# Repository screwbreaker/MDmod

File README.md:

# MDmod
Yes, another Mega Drive switchless mod

### Summary
This is another version of the classic switchless MOD for Mega Drive/Genesis.
There are two version of this MOD.
One for Padauk microcontrollers. And one for the old PIC16F630.
For each micro there is a little PCB for help in the installation.

### History
Everything started because I got some Padauk microcontrollers, and I wanted to play with them.
I choose to implement the Mega Drive switchless mod, because it seem very appropriate, as a basic program for microcontrollers.

Unfortunately, I've never enought free time to work on this project.
When I finally managed to make it the padauk microcontrollers where out of stock.
They still cheap, but not easy to found now.
So, since SDCC also handle PIC microcontrollers, I thought it was nice to port the code for the old PIC16F630.

I also made some little PCB, to make the installation simpler.

That's it, that's why now there is another, or better, onother two switchless mod for Mega Drive.

### How it work
This version is very simple, it only allow to switch between the different regions, JP, USA, EU
There is no way to change only the region or only the video mode.

#### How to change region
Hold down the reset button.
After 2 seconds the region led start to blink fast.
The region shown change every second.
To confirm the region release the reset button.
The region led blink three times to confirm the selection.

#### Normal reset
Press the reset button for less than 2 seconds.

### BOM
Only few components, the micro, a decoupling capacitor, and a resistor for the LEDs.
- C: 100 nF 0805 capacitor
- R: 0805 resistor

### Warning
The PCB are not the same!
The two microcontroller have the same package but a different pinout.
So, each micro have his own board, don't mix them!

Do not close both CC and CA jumpers!

### LED
For the LED resistor I suggest a 10K resistor, but the value can be choose according to the particular LED used.
Just beware to do not exceed the maximum current for the microcontroller pin.
For more information, read the datasheet of the microcontroller.

The mode is writed for an RGB LED.
Other mods use two color led, this is not the case. You must use an RGB led.
Or, another way is to keep the original red led, and place antoher led near it.

The mod allow to use both common anode, or common cathode LEDs.
There is a little jumper on the board that allow to choose the LED type, the jumpers are marked as CA (common anode), CC (common cathode).
Do not close both jumpers!!!

The COM pad is the common, wich can be either VCC or GND, depens on which jumper is set.

### Mega CD mode
This mod expose two pins to control the switchless mod for the MCD.
The pins output are inverted respect the language and video pins, this is for compatibility with other mods.
Is possible to configure the mod to reset the console automatically after a region switch.
To enable the auto reset close the MCD jumper.

When the MCD mode is enabled the console is set in reset before set the language and video pins.
This is made to avoid unwanted access to the MCD bios meanwhile the eeprom is set to a different memory map.
However the microcontroller can't keep the Mega Drive in reset by holding the reset signal.
The reset signal is generated internally every time the button is pressed, the reset time is fixed and can't be extended.

### Reset issue
Sometime during a region change, an unwanted reset can happen.
The mod use a debounce to avoid this. But this is also dependant from the lenght of the wire from the reset button.
If you have such isse, increase the debounce delay in the firmware. Or, put a 100nF capacitor between the reset singal and GND (as close as possible to the micro).

### Padauk VS PIC
No differences, but the PIC also have an internal EPROM, so it can save the last mode used.
The padauk can't. The micro always start with the default region. The default region must be set in the firmware.

### Installation
Exactly like any other switchless MOD.
There are plenty guide online, they are well made, and cover all the Mega Drive/Genesis variants.
So, I'm not going to rewrite a guide.

Bot the boards are singe side, so the PCB back can be put in cotact with the Mega Drive board without issue.

### License
The PCBs are under the CERN OHL license.
The firmwares, under the GPL3.

This is an OPEN project.
So, like any other project like this, the hope is that others can improve it an reshare with the community.
Don't go out this basic guideline.

### Disclaimer
The hardware and the software are provided to you 'as is' and without any express or implied warranties whatsoever with respect to its functionality, operability or use, including, without limitation, any implied warranties of merchantability, fitness for a particular purpose or infringement. We expressly disclaim any liability whatsoever for any direct, indirect, consequential, incidental or special damages, including, without limitation, lost revenues, lost profits, losses resulting from business interruption or loss of data, regardless of the form of action or legal theory under which the liability may be asserted, even if advised of the possibility or likelihood of such damages.

### Thanks
- Thanks to the guys of the [Free PDK](https://free-pdk.github.io/) project. They are really smart and awesome!

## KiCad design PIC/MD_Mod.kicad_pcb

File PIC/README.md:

# MDmod PDK
Mega Drive switchless MOD for Padauk microcontroller

### Summary
This mod is writted for the PIC16F630 microcontroller.
This mod is written with the SDCC. Maybe the SDCC is not the best for PIC, but it do the job very well.

### How to compile and program
This MOD must be compiled with [SDCC](http://sdcc.sourceforge.net/).
To program the micro I suggest the [Minipro/XGecu](http://www.xgecu.com/en/) programmer.
But i'm sure it can be programmed with the PICKit.

To compile use the "--use-non-free" parameter.
Or use the MAKEFILE in the firmware directory.

### License
The PCBs are under the CERN OHL license.
The firmwares, under the GPL3.

This is an OPEN project.
So, like any other project like this, the hope is that others can improve it an reshare with the community.
Don't go out this basic guideline.

### Disclaimer
The hardware and the software are provided to you 'as is' and without any express or implied warranties whatsoever with respect to its functionality, operability or use, including, without limitation, any implied warranties of merchantability, fitness for a particular purpose or infringement. We expressly disclaim any liability whatsoever for any direct, indirect, consequential, incidental or special damages, including, without limitation, lost revenues, lost profits, losses resulting from business interruption or loss of data, regardless of the form of action or legal theory under which the liability may be asserted, even if advised of the possibility or likelihood of such damages.

### Thanks
- The [SDCC](http://sdcc.sourceforge.net/) team.

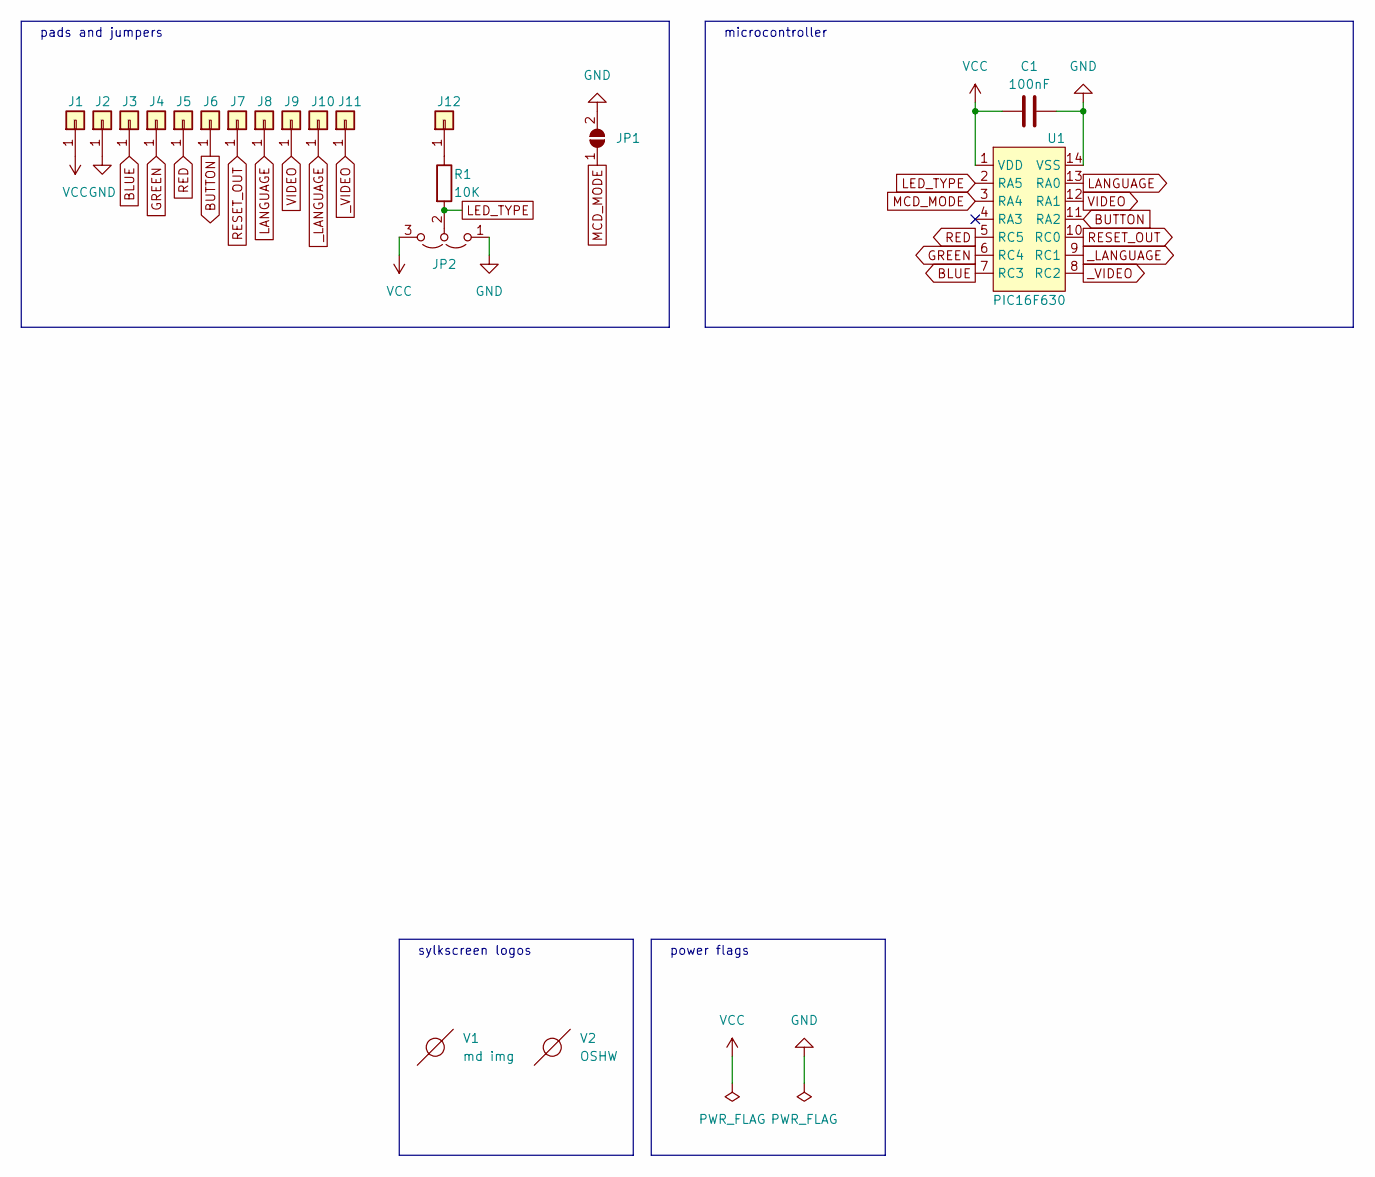
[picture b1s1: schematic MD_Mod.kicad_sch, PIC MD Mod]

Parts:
C1: 100nF; C_0805_2012Metric_Pad1.18x1.45mm_HandSolder; Manufacturer_Part_Number CC0805KRX7R9BB104
J1, J2, J3, J4, J5, J6, J7, J8, J9, J10, J11, J12: Conn_01x01; pad
JP1: SolderJumper_2_Open; SolderJumper-2_P1.3mm_Open_TrianglePad1.0x1.5mm
JP2: Jumper_3_Open; SolderJumper-3_P2.0mm_Open_TrianglePad1.0x1.5mm
R1: 10K; R_0805_2012Metric_Pad1.20x1.40mm_HandSolder; Manufacturer_Part_Number 0805S8J0103T5E
U1: PIC16F630; SOIC-14_3.9x8.7mm_P1.27mm; Manufacturer_Part_Number PIC16F630-I/SL
V1: md img; md_pic
V2: OSHW

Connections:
BLUE: J3.1, U1.7 (RC3)
BUTTON: J6.1, U1.11 (RA2)
GND: C1.2, J2.1, JP1.2 (B), JP2.1 (A), U1.14 (VSS)
GREEN: J4.1, U1.6 (RC4)
LANGUAGE: J8.1, U1.13 (RA0)
LED_TYPE: JP2.2 (C), R1.2, U1.2 (RA5)
MCD_MODE: JP1.1 (A), U1.3 (RA4)
unnamed: J12.1, R1.1
RED: J5.1, U1.5 (RC5)
RESET_OUT: J7.1, U1.10 (RC0)
VCC: C1.1, J1.1, JP2.3 (B), U1.1 (VDD)
VIDEO: J9.1, U1.12 (RA1)
_LANGUAGE: J10.1, U1.9 (RC1)
_VIDEO: J11.1, U1.8 (RC2)

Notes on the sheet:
microcontroller
pads and jumpers
sylkscreen logos
power flags

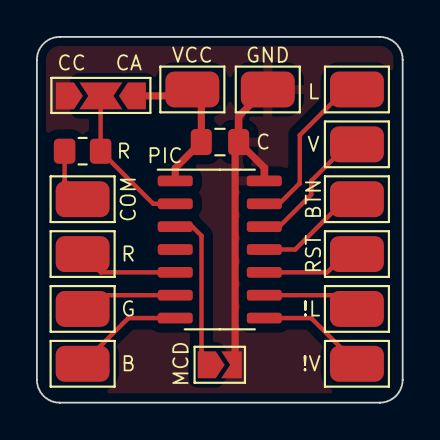
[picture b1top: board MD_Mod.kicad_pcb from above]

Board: 2 copper layers, 20.3 x 20.3 mm, 19 parts (2 on the bottom side), 14 nets.

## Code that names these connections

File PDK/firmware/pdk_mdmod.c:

/* Mega Drive switchless mod for Padauk ICs, to be compiled with SDCC.
 * 
 * made by screwbreaker
 * rev 1.0
 *
 * SYNOPSIS:
 * Yes, another switchless mod for Mega Drive
 * this version is very simple, it only allow to switch between the different regions, JP, USA, EU
 * there is no way to change only the region or the video mode
 *
 * HOW TO CHANGE REGION:
 * hold down the reset button
 * after 2 seconds the region led start to blink fast
 * the region shown change every second
 * to confirm the region release the reset button
 * the region led blink three times to confirm the selection
 *
 * NORMAL RESET:
 * press the reset button for less than 2 seconds
 *
 * MEGA CD MODE:
 * this mod expose two pins to control the switchless mod for the MCD
 * the pins output are inverted respect the language and video pins, this is for compatibility with other mods
 * is possible to configure the mod to reset the console automatically after a region switch
 * to enable the auto reset connect the MCD pin to ground
 *
 * when the MCD mode is enabled the console is set in reset before set the language and video pins
 * this is made to avoid unwanted access to the MCD bios meanwhile the eeprom is set to a different memory map
 * however the microcontroller can't keep the Mega Drive in reset by holding the reset signal
 * the reset signal is generated internally every time the button is pressed, the reset time is fixed and can't be extended
 * there are other reset singals inside the mega drive, this is used by games or expansions to control the reset signal
 * this mod expose a second reset pin, to allow to control other reset signal inside the console
 * this pin is an open drain, is intended to be put in parallel to the other devices
 * this feature is for future use or test only, do not use it at the moment
 *
 * LED DRIVE TYPE:
 * is possible to choose either a common anode or a common cathode LED
 * one pin is used to choose the led type, the pin is tied to VCC with the internal pull-up
 * if not connected the default choose is for a commmon anode led
 *
 * check the datasheet for the microcontroller to check the maximum current to drive the LEDS
 * LEDs generally needs a very small current, expecially if used as indicator like in this case
 * my suggestion is to drive them with the smallest current as possible, no more than 5ma
 */

/* includes */
#include "pdk.h"
#include "utils.h"

/* global defines */
#define DEFAULT_REGION EU	// This is the default region used on the first boot

// pin settings
#define RED		PA,7	// red LED
#define GREEN		PA,6	// green LED
#define BLUE		PA,5	// blue LED

#define VIDEO		PB,1	// video (50/60Hz)
#define LANGUAGE	PB,2	// language (ENG/JAP)
#define _VIDEO		PA,3	// inverted video (For Mega CD)
#define _LANGUAGE	PA,4	// inverted language (For Mega CD)
#define RESET		PA,0	// reset output
#define BUTTON		PB,0	// reset button in
#define MCD		PB,6	// if low enable the Mega CD mode, reset the console after a region change
#define LED_TYPE	PB,5	// HIGH = common anode, LOW = common cathode

/* do not modify anything under this line */

#define ledOn(led)	bools.led_type ? (clearBit(led)) : (setBit(led))
#define ledOff(led)	bools.led_type ? (setBit(led)) : (clearBit(led))

#define isBtnPressed	isPinLow
#define reset()		bools.reset = true; \
			delay = RESET_DELAY
#define next_region()	region = ((region + 1) % REGIONS)

#define RESET_DELAY	33	// about 270ms
#define DEBOUNCE_DELAY	5	// about 40ms
#define CHANGE_TIME	200	// about 1.6 sec with 8ms tick
#define LED_FAST_DELAY	16	// about 130ms with 8ms tick
#define LED_SLOW_DELAY	33	// about 270ms with 8ms tick
#define SHOW_TURNS	8	// about 1s
#define CONFIRM_TURNS	5	// 3 slow blinks

#define ALL_OFF REGIONS

/* global typedefs and structures */
typedef union {
	struct {
		unsigned tick		: 1;
		unsigned btn_event	: 1;
		unsigned show_regions	: 1;
		unsigned confirm_region	: 1;
		unsigned reset		: 1;
		unsigned led_state	: 1;
		unsigned mcd		: 1;
		unsigned led_type	: 1;
	};

	struct {
		unsigned BOOLS		: 8;
	};
} __Bools_t;

typedef enum {
	JP = 0x00,
	EU,
	US,
	REGIONS
} region_t;

/* functions prototypes */
void set_led(region_t region);
void set_region(void);
void set_mcd(void);

/* global variables */
volatile region_t region = DEFAULT_REGION;
volatile __Bools_t bools;
volatile uint8_t turns = 0;
volatile uint8_t delay = 0;
volatile uint8_t debounce_delay = 0;
volatile uint32_t btn_counter = 0;

// interrupt handler (kept as simple/minimalistic as possible)
void interrupt(void) __interrupt(0) {
	// monitor the MD reset button
	if (INTRQ & INTRQ_PB0) {
		if (!debounce_delay) {
			debounce_delay = DEBOUNCE_DELAY;
			bools.btn_event = true;
			INTRQ &= ~INTRQ_PB0;
		}
	}

	// when T16 'ticks'
	if (INTRQ & INTRQ_T16) {
		bools.tick = true;
		INTRQ &= ~INTRQ_T16;
	}
}

unsigned char _sdcc_external_startup(void) {
	// setup 8MHz sysclock and let easypdk programmer do the calibration (after writing)
	EASY_PDK_INIT_SYSCLOCK_8MHZ();		//use 8MHz sysclock
	EASY_PDK_CALIBRATE_IHRC(8000000,5000);	//tune SYSCLK to 8MHz @ 5.000V
	EASY_PDK_CALIBRATE_BG();
	EASY_PDK_FUSE(FUSE_BOOTUP_FAST | FUSE_SECURITY_OFF);
	return 0;
}

// timers and pin setup
void setup() {
	setPinOutput(RED);
	setPinOutput(GREEN);
	setPinOutput(BLUE);

	setPinOutput(VIDEO);
	setPinOutput(LANGUAGE);
	setPinOutput(_VIDEO);
	setPinOutput(_LANGUAGE);

	setPinOutput(RESET);
	setPin(RESET);

	enableDigitalInput(LED_TYPE);
	setPinPullup(LED_TYPE);

	enableDigitalInput(MCD);
	setPinPullup(MCD);

	enableDigitalInput(BUTTON);
	setPinPullup(BUTTON);

	// enable T16 timer to generate an interrupt about every 8 milliseconds
	T16M = T16_CLK_IHRC | T16_CLK_DIV64 | T16_INTSRC_10BIT;	// Use IHRC clock source (16 MHz), /64, Interrupt on (rising) Bit 10
	INTEN = INTEN_T16| INTEN_PB0;
	INTEGS = INTEGS_T16_RISING | INTEGS_PB0_BOTH;

	// enable interrupts
	INTRQ = 0;
	__engint();	// enable global interrupts
} // setup()

void main(void) {
	// Setup pin and timers
	setup();

	// read the Mega CD mode pin
	bools.mcd = isPinLow(MCD);

	// read the type of led used
	bools.led_type = isPinHigh(LED_TYPE);

	// set default region
	set_region();
	set_led(DEFAULT_REGION);

	//reset(); // reset the MD to be sure region pins are read correctly // uncomment if there is trouble at boot

	while(true) {
		// handle the timers
		if (bools.tick) {
			bools.tick = false;

			if (bools.btn_event) {
				btn_counter++;
			}

			if (debounce_delay) {
				debounce_delay--;
			}

			if (delay) {
				delay--;
			}
		}

		// the RESET button is pressed / released
		if (bools.btn_event) {
			if (!debounce_delay) {
				if (isBtnPressed(BUTTON)) {
					if (btn_counter > CHANGE_TIME) {
						bools.show_regions = true;
					}
				} else {
					bools.btn_event = false;

					if (btn_counter > CHANGE_TIME) {
						turns = 0;
						bools.show_regions = false;
						bools.confirm_region = true;
					} else {
						reset();
					}

					btn_counter = 0;
				}
			}
		}

		// each led blink fast for a while
		if (bools.show_regions) {
			if (delay == 0) {
				if (bools.led_state) {
					set_led(region);
				} else {
					set_led(ALL_OFF);
				}

				if (turns > SHOW_TURNS) {
					next_region();
					turns = 0;
				} else {
					turns++;
				}

				bools.led_state = !bools.led_state;
				delay = LED_FAST_DELAY;
			}
		}

		// the LED of the choosed region make few slow blinks, to confirm the selection
		if (bools.confirm_region) {
			if (delay == 0) {
				if (bools.led_state) {
					set_led(region);
				} else {
					set_led(ALL_OFF);
				}

				if (turns > CONFIRM_TURNS) {
					turns = 0;
					delay = 0;
					bools.confirm_region = false;
					set_led(region);
					set_region();
				} else {
					turns++;
				}

				bools.led_state = !bools.led_state;
				delay = LED_SLOW_DELAY;
			}
		}

		// keep the reset singal low for a while, then release it
		if (bools.reset) {
			if (delay) {
				clearPin(RESET);
			} else {
				setPin(RESET);
				bools.reset = false;
			}
		}
	}
}

// set region
void set_region(void) {
	switch(region) {
		case JP:
			clearPin(LANGUAGE);
			setPin(VIDEO);
			break;
		case EU:
			setPin(LANGUAGE);
			clearPin(VIDEO);
			break;
		case US:
			setPin(LANGUAGE);
			setPin(VIDEO);
			break;
		default:
			break;
	}

	set_mcd();
} // set_region()

// set MCD bios
void set_mcd(void) {
	if (bools.mcd) {
		clearPin(RESET);
		reset();
	}

	switch(region) {
		case JP:
			setPin(_LANGUAGE);
			clearPin(_VIDEO);
			break;
		case EU:
			clearPin(_LANGUAGE);
			setPin(_VIDEO);
			break;
		case US:
			clearPin(_LANGUAGE);
			clearPin(_VIDEO);
			break;
		default:
			break;
	}
} // set_mcd()

// set LED
void set_led(region_t region) {
	switch(region) {
		case JP:
			ledOff(GREEN);
			ledOff(BLUE);
			ledOn(RED);
			break;
		case EU:
			ledOff(RED);
			ledOff(BLUE);
			ledOn(GREEN);
			break;
		case US:
			ledOff(GREEN);
			ledOff(RED);
			ledOn(BLUE);
			break;
		default:
			ledOff(RED);
			ledOff(GREEN);
			ledOff(BLUE);
			break;
	}
} // set_led()

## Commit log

2022-07-03 Update LICENSE
2022-07-03 Create empty
